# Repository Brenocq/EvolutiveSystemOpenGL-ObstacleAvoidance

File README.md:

# Evolutive System OpenGL - Obstacle Avoidance

Parallel evolution study of sensors and brain using OpenGL to simulate and Qt to generate graphs.

## Introduction
This project is the result of a scientific initiation with Professor Eduardo Simões (USP-ICMC) and is still under development. Initially, I started developing a simple GA for obstacle avoidance and exploration using 3 distance sensors as input, but the robots were evolving very quickly which was not interesting for analysis. In order to make the system more complex we are adding a neural network to the sensor analysis system. More info in the future.

## Installation
First, you need to download the OpenGl and Glut:
```
$ sudo apt-get install mesa-common-dev
$ sudo apt-get install freeglut3-dev

$ git clone https://github.com/Brenocq/EvolutiveSystemOpenGL-ObstacleAvoidance.git

```
## Running
When executing the program it is possible to choose in which file the data will be saved.
```
$ cd EvolutiveSystemOpenGL-ObstacleAvoidance/src
$ make
$ ./run <FILE_NAME>
```
You can also use `make run` to compile and execute at the same time.
## License
This project is licensed under the MIT License - see the [LICENSE.md](https://github.com/Brenocq/EvolutiveSystemOpenGL-ObstacleAvoidance/blob/master/LICENSE) file for details.

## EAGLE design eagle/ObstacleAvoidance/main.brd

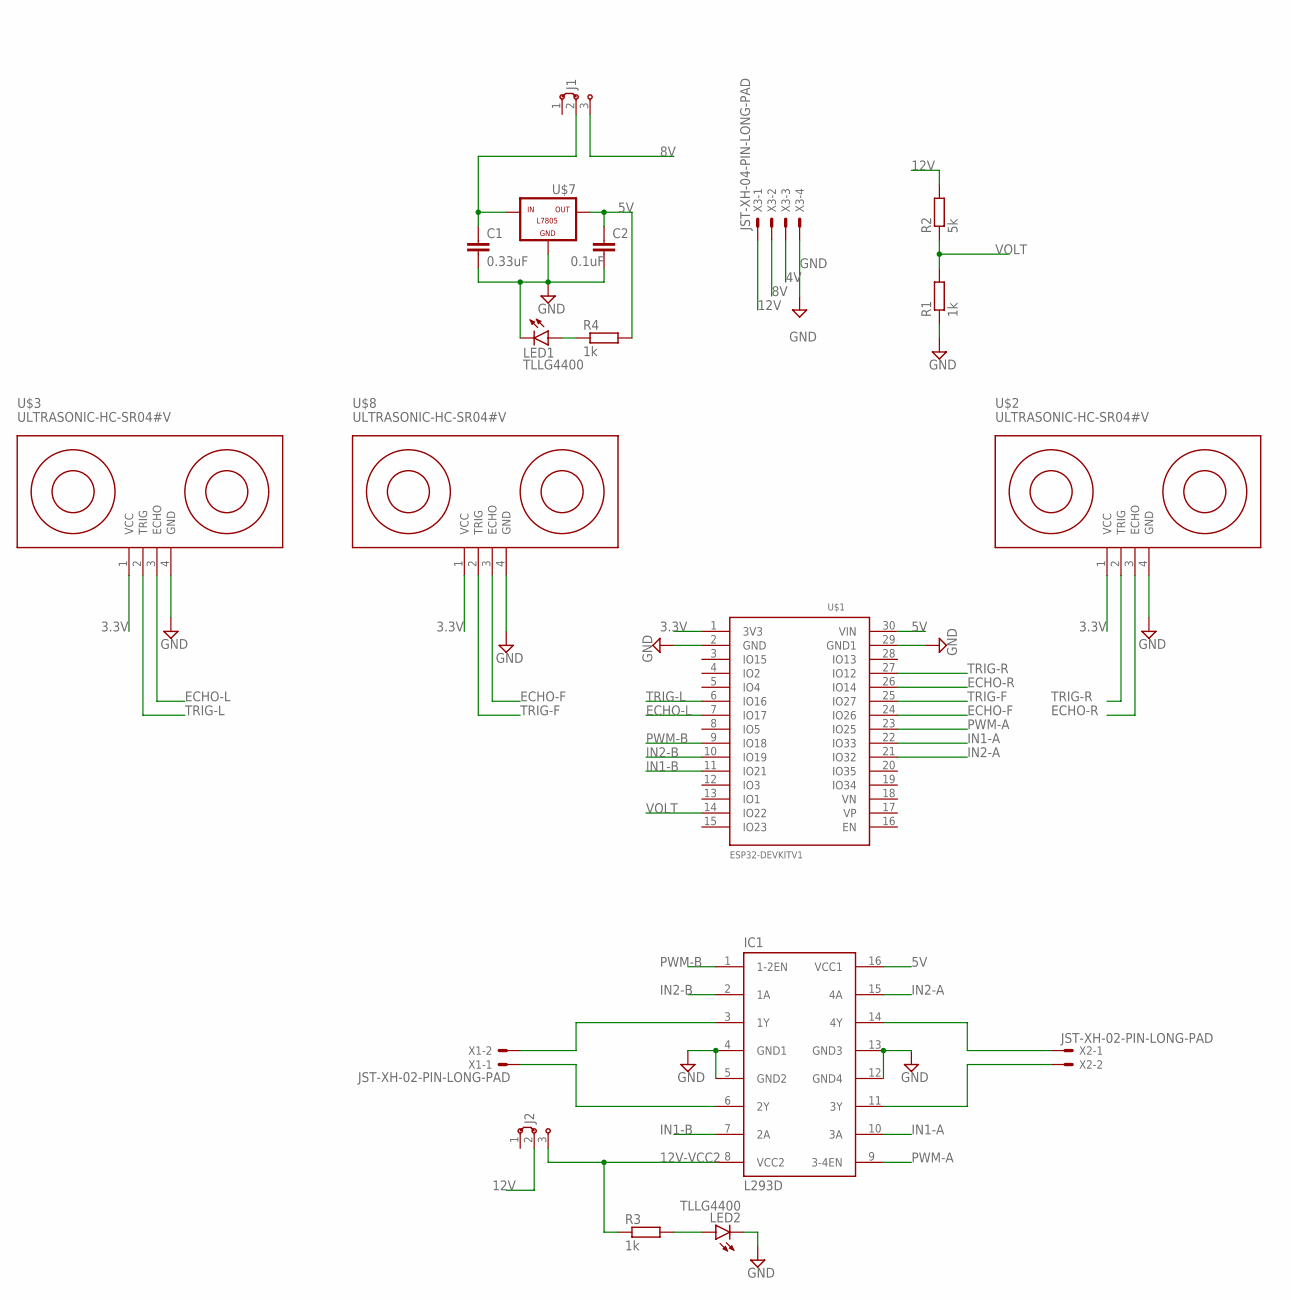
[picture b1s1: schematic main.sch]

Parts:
C1: 0.33uF; C2.5-3
C2: 0.1uF; C2.5-3
IC1: L293D; DIL16
J1, J2: J2X5MM; 05C
LED1, LED2: TLLG4400; LED3MM
R1, R3, R4: 1k; 0207/10
R2: 5k; 0207/10
U$1: ESP32DEVKITV1; ESP32-DEVKITV1
U$2, U$3, U$8: ULTRASONIC-HC-SR04#V
U$7: -L7805; L7805
X1, X2: JST-XH-02-PIN-LONG-PAD; JST-XH-02-PACKAGE-LONG-PAD
X3: JST-XH-04-PIN-LONG-PAD; JST-XH-04-PACKAGE-LONG-PAD

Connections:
3.3V: U$1.1 (3V3), U$2.1 (VCC), U$3.1 (VCC), U$8.1 (VCC)
4V: X3.3
5V: C2.1, IC1.16 (VCC1), R4.2, U$1.30 (VIN), U$7.OUT
8V: J1.3, X3.2
12V: J2.2, R2.2, X3.1
12V-VCC2: IC1.8 (VCC2), J2.3, R3.1
ECHO-F: U$1.24 (IO26), U$8.3 (ECHO)
ECHO-L: U$1.7 (IO17), U$3.3 (ECHO)
ECHO-R: U$1.26 (IO14), U$2.3 (ECHO)
GND: C1.2, C2.2, IC1.4 (GND1), IC1.5 (GND2), IC1.12 (GND4), IC1.13 (GND3), LED1.K (C), LED2.K (C), R1.1, U$1.2 (GND), U$2.4 (GND), U$3.4 (GND), U$7.GND, U$8.4 (GND), X3.4
IN1-A: IC1.10 (3A), U$1.22 (IO33)
IN1-B: IC1.7 (2A), U$1.11 (IO21)
IN2-A: IC1.15 (4A), U$1.21 (IO32)
IN2-B: IC1.2 (1A), U$1.10 (IO19)
unnamed: IC1.3 (1Y), X1.2
unnamed: IC1.6 (2Y), X1.1
unnamed: IC1.14 (4Y), X2.1
unnamed: IC1.11 (3Y), X2.2
unnamed: LED1.A, R4.1
unnamed: C1.1, J1.2, U$7.IN
unnamed: LED2.A, R3.2
PWM-A: IC1.9 (3-4EN), U$1.23 (IO25)
PWM-B: IC1.1 (1-2EN), U$1.9 (IO18)
TRIG-F: U$1.25 (IO27), U$8.2 (TRIG)
TRIG-L: U$1.6 (IO16), U$3.2 (TRIG)
TRIG-R: U$1.27 (IO12), U$2.2 (TRIG)
VOLT: R1.2, R2.1, U$1.14 (IO22)

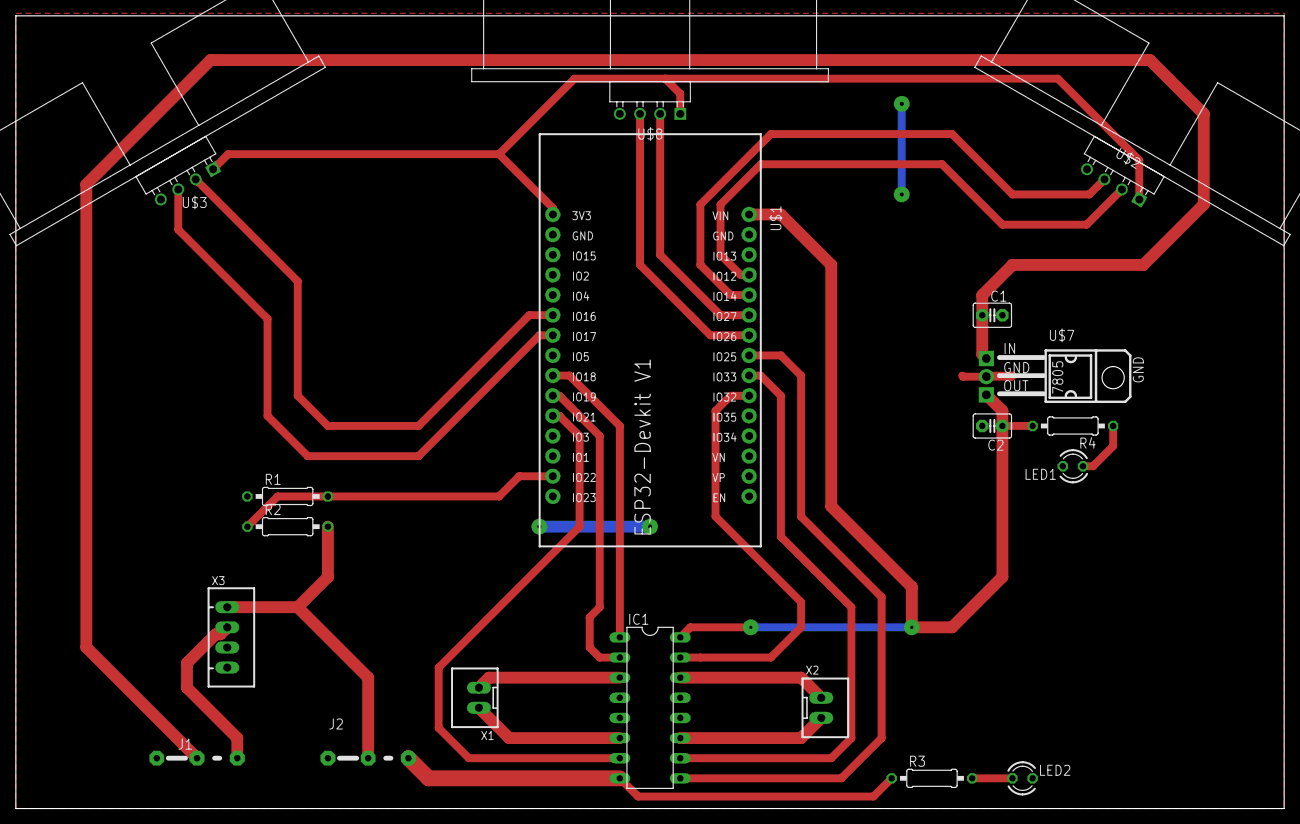
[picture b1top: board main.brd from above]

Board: 2 copper layers, 160.0 x 100.0 mm, 19 parts (0 on the bottom side), 26 nets.

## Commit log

2019-07-02 Test: Animation with OpenGL
2019-07-06 Feat: Show robots with OpenGL
2019-07-06 Feat: Robots with distance sensors
2019-07-07 Feat: Detect walls with sensors
2019-07-08 Feat: obstacles
2019-07-08 Refeat: Object detection with sensors
2019-07-10 Feat: Multiples environments
2019-07-10 Feat: Environment mutation
2019-07-12 Refeat: Faster simulations
2019-07-20 Fix: Object class build error
2019-07-25 Style: Organizing Classes
    Best organization for Robot and Environment
2019-08-03 Refactor: Saving old work
2019-08-13 Style: OOP organization
2019-08-13 Feat: Matlab application
2019-08-24 Refeat: Output file with header info
2019-09-03 Feat: Quadtree collision
2019-09-08 Feat: Show QuadTree
2019-09-21 Feat: Select population QT
2019-09-22 Feat: Plot robot evolution
2019-09-22 Feat: Parellelize with OpenMP
2019-09-22 Refeat: Without quadtree
2019-10-05 Refeat: Fitness evaluation
    Can fix gene values
    Calculate fitness each X seconds
    Changed obstacle avoidance method
2019-10-05 Refeat: Red when robot collision
    Changed graph min/max Y (QT)
    Deleted comments
2019-10-08 Create LICENSE
2019-10-10 Style: Deleted extra files
2019-10-10 Docs: Gif release v1.0
2019-10-10 Auto stash before merge of "master" and "origin/master"
2019-10-11 Feat: brain and anatomy genes
2019-10-16 Docs: Introduction and how to run
2019-10-16 Feat: From IR sensor to simplified sensor
2019-10-17 Refeat: Sensor and brain improvement
    Better sensor angle
    Brain sum "normalization"
2019-10-17 Refeat: Changed evolution parameters
    Robot only positive velocity
    New collision calculation
    Changed mutation brain
2019-10-17 'Better' obstacles
    Changed the color of the obstacles, as well as random size for them
2019-10-18 Refeat: Improved brain rotation
    Robots colors
    Parameters changed
2019-10-18 Feat: Click to speed up simulation
    Fix core dump too
    Added exploration points
2019-10-28 Feat: 3 Sensors evolution working
2019-10-29 Feat: Write sensor info to file
2019-11-03 Feat: Select robots to plot
2019-11-16 Feat: Data generation
2019-11-22 Fix: Slow application
2019-11-22 Feat: PCB files
2019-11-24 Feat: .ignore
2019-11-24 Feat: Eagle pcb
2019-11-24 Feat: .gitignore
2019-11-25 Feat: PCB battery connector
2019-11-27 Feat: Deleted folders
2019-12-09 Feat: Added immunity
2019-12-10 Test: Max time generation
2019-12-18 Feat: Graph resizing

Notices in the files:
parts and their libraries:
diy-modules: Released under the Creative Commons Attribution 4.0 International License: http://creativecommons.org/licenses/by/4.0
